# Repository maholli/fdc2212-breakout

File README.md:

# fdc2212-breakout
Breakout board for TI FDC2212 capacitance-to-digital chip

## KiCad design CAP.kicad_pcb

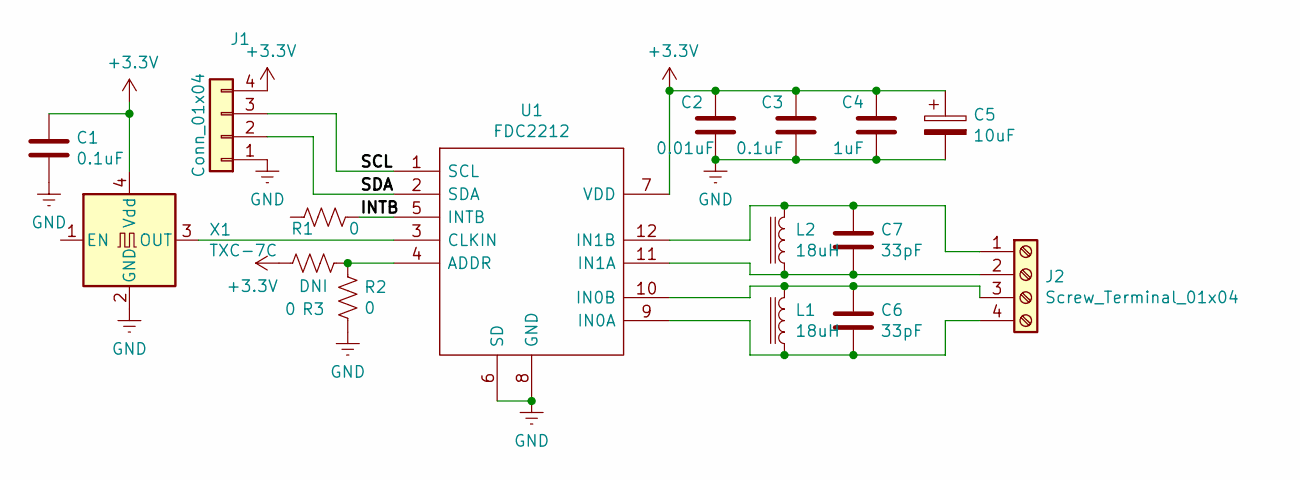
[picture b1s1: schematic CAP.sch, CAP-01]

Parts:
C1, C3: 0.1uF; C_0402_1005Metric
C2: 0.01uF; C_0402_1005Metric
C4: 1uF; C_0402_1005Metric
C5: 10uF; CP_EIA-2012-15_AVX-P
C6, C7: 33pF; C_0805_2012Metric
J1: Conn_01x04; PinHeader_1x04_P2.54mm_Vertical
J2: Screw_Terminal_01x04; TerminalBlock_TE_282834-4_1x04_P2.54mm_Horizontal
L1, L2: 18uH; L_1210_3225Metric; Part Number CMH322522
R1, R2, R3: 0; R_0402
U1: FDC2212; SON50P400X400X80-13N; Manufacturer_Part_Number FDC2212DNTT; Mouser Part Number 595-FDC2212DNTT
X1: TXC-7C; Oscillator_SMD_TXC_7C-4Pin_5.0x3.2mm

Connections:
+3V3: C1.1, C2.1, C3.1, C4.1, C5.1, J1.4, R3.2, U1.7 (VDD), X1.4 (Vdd)
/INTB: R1.1, U1.5 (INTB)
/SCL: J1.3, U1.1 (SCL)
/SDA: J1.2, U1.2 (SDA)
GND: C1.2, C2.2, C3.2, C4.2, C5.2, J1.1, R2.2, U1.6 (SD), U1.8 (GND), U1.13 (EP), X1.2 (GND)
unnamed: C6.1, J2.3, L1.2, U1.10 (IN0B)
unnamed: C6.2, J2.4, L1.1, U1.9 (IN0A)
unnamed: C7.1, J2.1, L2.2, U1.12 (IN1B)
unnamed: C7.2, J2.2, L2.1, U1.11 (IN1A)
unnamed: R2.1, R3.1, U1.4 (ADDR)
unnamed: U1.3 (CLKIN), X1.3 (OUT)

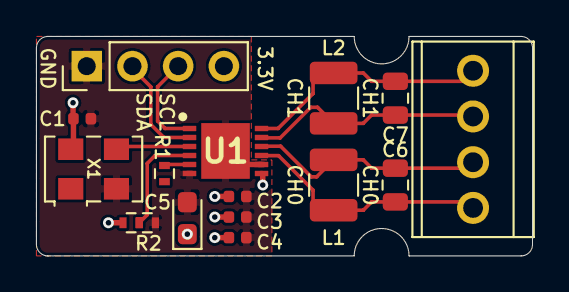
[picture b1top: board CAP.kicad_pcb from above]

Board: 2 copper layers, 27.6 x 12.2 mm, 16 parts (0 on the bottom side), 11 nets.

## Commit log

2019-07-03 layout files
